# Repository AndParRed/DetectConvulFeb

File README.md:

# DetectConvulFeb
Repositorio de los codigos fuentes del Detector de convulsiones febriles y su APP Android

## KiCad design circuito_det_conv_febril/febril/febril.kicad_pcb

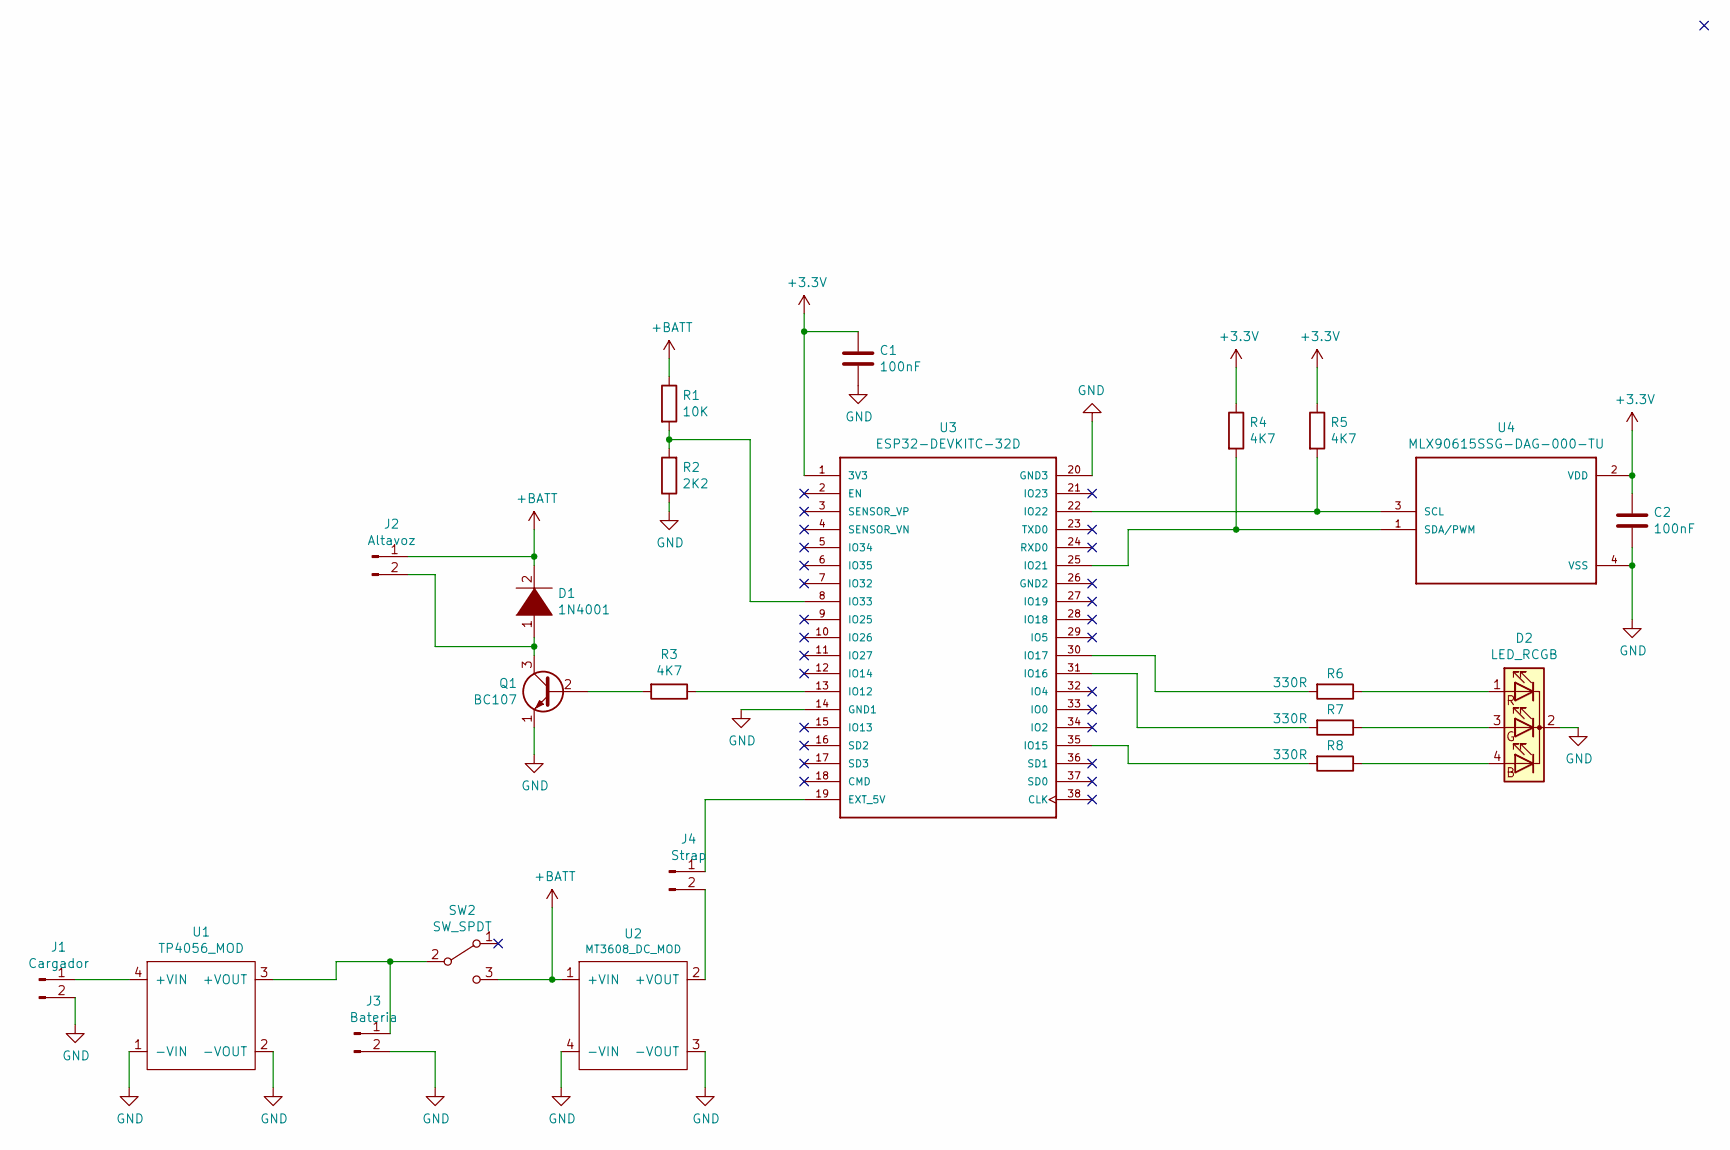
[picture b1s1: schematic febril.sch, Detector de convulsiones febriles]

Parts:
C1, C2: 100nF; C_Disc_D4.7mm_W2.5mm_P5.00mm
D1: 1N4001; D_DO-41_SOD81_P10.16mm_Horizontal
D2: LED_RCGB; LED_D5.0mm-4_RGB
J1: Cargador; PinHeader_1x02_P2.54mm_Vertical
J2: Altavoz; PinHeader_1x02_P2.54mm_Vertical
J3: Bateria; PinHeader_1x02_P2.54mm_Vertical
J4: Strap; PinHeader_1x02_P2.54mm_Vertical
Q1: BC107; TO-18-3
R1: 10K; R_Axial_DIN0207_L6.3mm_D2.5mm_P10.16mm_Horizontal
R2: 2K2; R_Axial_DIN0207_L6.3mm_D2.5mm_P10.16mm_Horizontal
R3, R4, R5: 4K7; R_Axial_DIN0207_L6.3mm_D2.5mm_P10.16mm_Horizontal
R6, R7, R8: 330R; R_Axial_DIN0207_L6.3mm_D2.5mm_P10.16mm_Horizontal
SW2: SW_SPDT; Switch_Toggle_ATE1D-2M3-10-Z
U1: TP4056_MOD
U2: MT3608_DC_MOD
U3: ESP32-DEVKITC-32D; MODULE_ESP32-DEVKITC-32D
U4: MLX90615SSG-DAG-000-TU; TO127P550H280-4

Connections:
+3V3: C1.1, C2.1, R4.1, R5.1, U3.1 (3V3), U4.2 (VDD)
+BATT: D1.2 (A), J2.1, R1.1, SW2.3 (C), U2.1 (+VIN)
GND: C1.2, C2.2, D2.2 (K), J1.2, J3.2, Q1.1 (E), R2.1, U1.1 (-VIN), U1.2 (-VOUT), U2.3 (-VOUT), U2.4 (-VIN), U3.14 (GND1), U3.20 (GND3), U4.4 (VSS)
unnamed: D1.1 (K), J2.2, Q1.3 (C)
unnamed: D2.1 (RA), R6.1
unnamed: D2.3 (GA), R7.1
unnamed: D2.4 (BA), R8.1
unnamed: J1.1, U1.4 (+VIN)
unnamed: J3.1, SW2.2 (B), U1.3 (+VOUT)
unnamed: J4.1, U3.19 (EXT_5V)
unnamed: J4.2, U2.2 (+VOUT)
unnamed: Q1.2 (B), R3.2
unnamed: R1.2, R2.2, U3.8 (IO33)
unnamed: R3.1, U3.13 (IO12)
unnamed: R4.2, U3.25 (IO21), U4.1 (SDA/PWM)
unnamed: R5.2, U3.22 (IO22), U4.3 (SCL)
unnamed: R6.2, U3.30 (IO17)
unnamed: R7.2, U3.31 (IO16)
unnamed: R8.2, U3.35 (IO15)

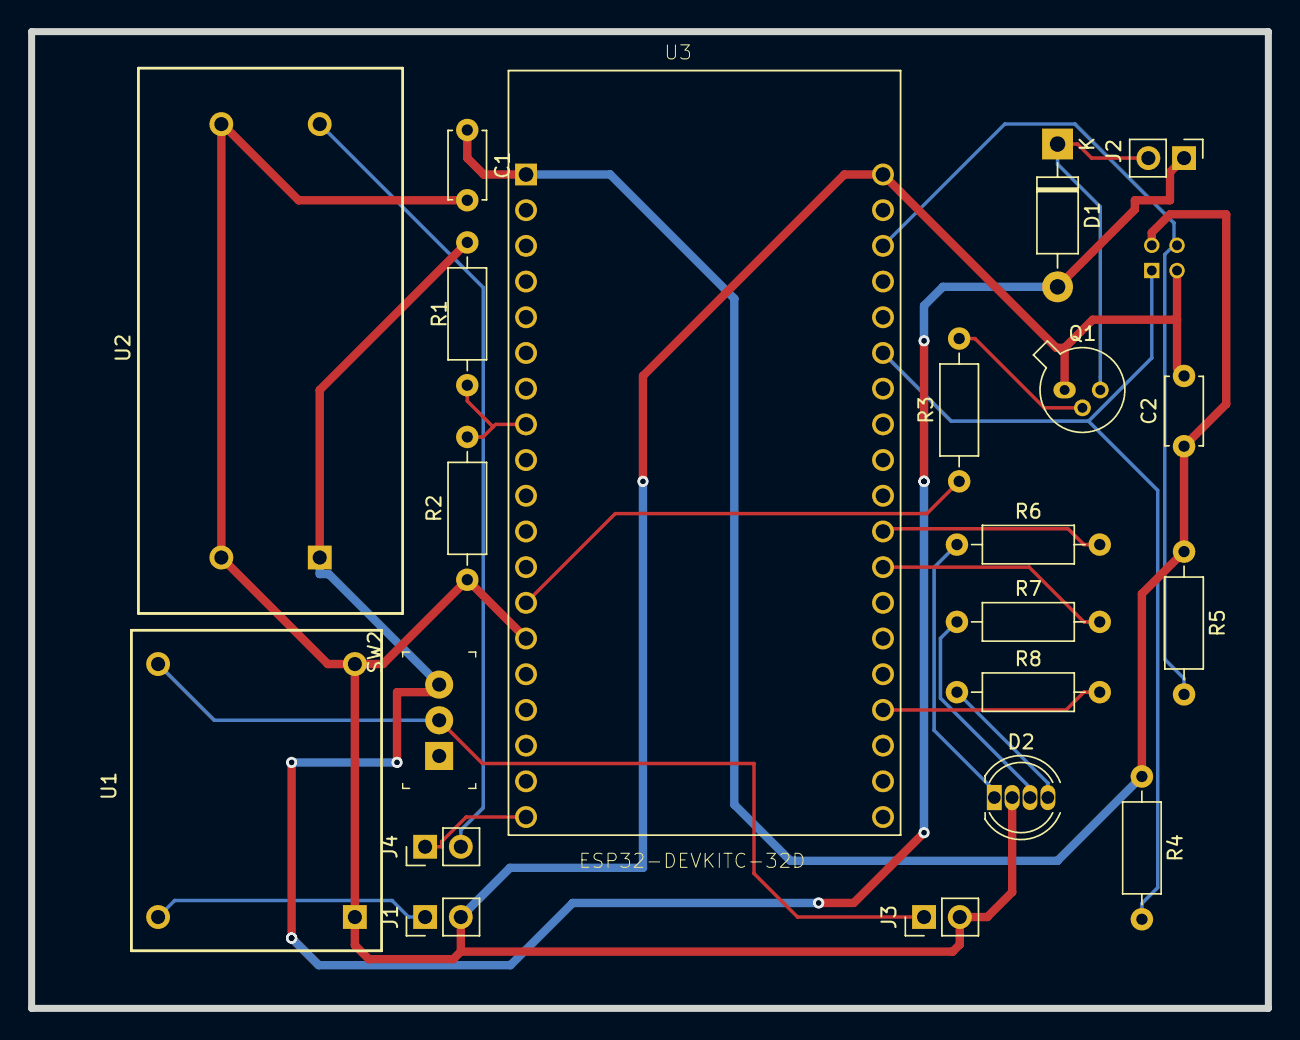
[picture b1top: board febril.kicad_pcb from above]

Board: 2 copper layers, 88.0 x 69.5 mm, 22 parts (1 on the bottom side), 19 nets.

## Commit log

2020-07-19 Version inicial.
